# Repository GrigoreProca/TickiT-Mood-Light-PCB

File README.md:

# TickiT Mood Light PCB
DIY TickiT PCB with WS2812B LEDs

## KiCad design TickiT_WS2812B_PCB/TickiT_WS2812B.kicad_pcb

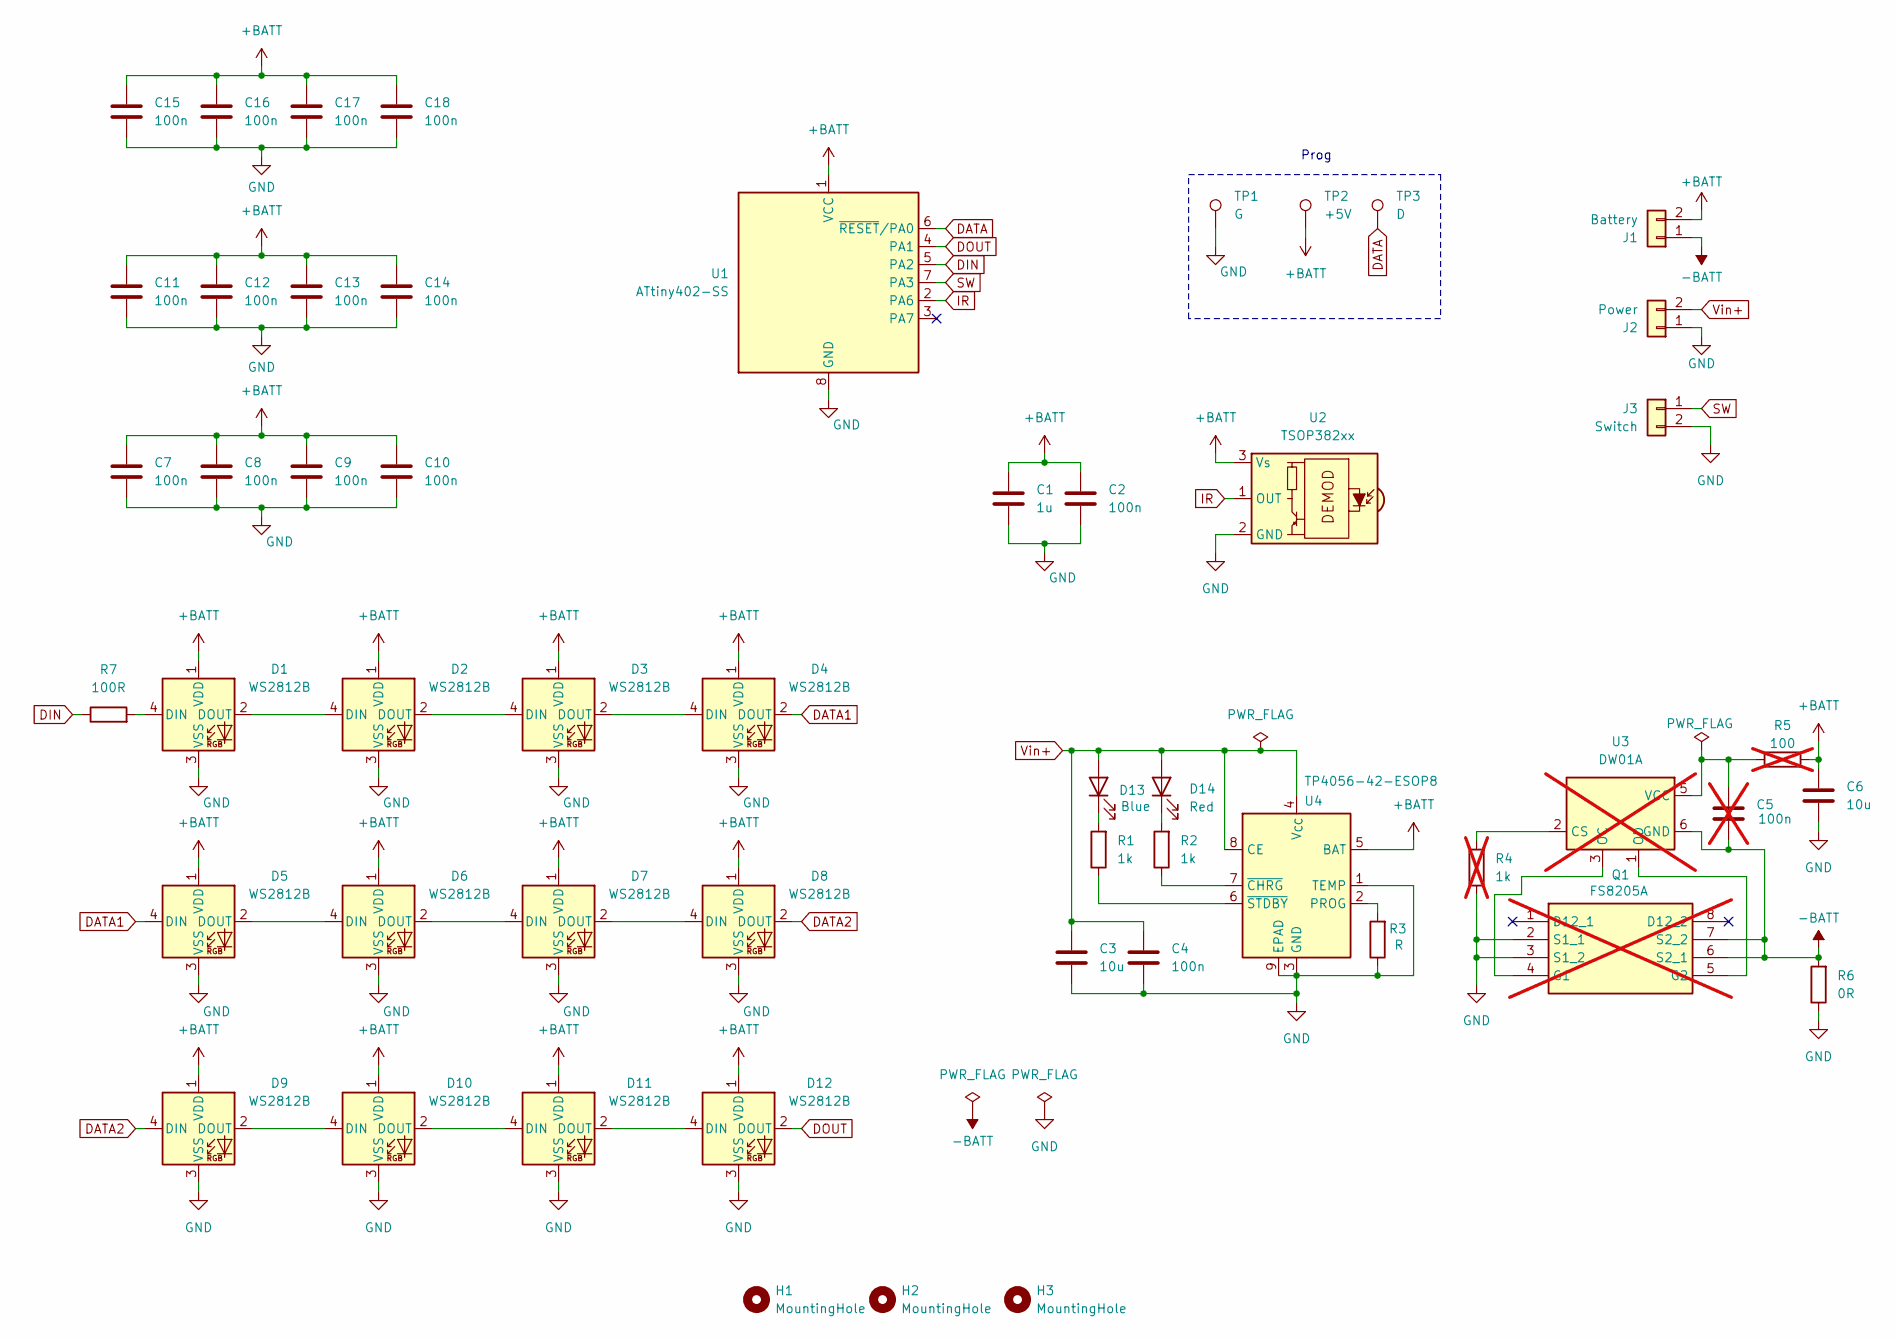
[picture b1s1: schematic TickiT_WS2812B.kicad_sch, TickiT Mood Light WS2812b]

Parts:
C1: 1u; C_0603_1608Metric_Pad1.08x0.95mm_HandSolder
C2, C4, C7, C8, C9, C10, C11, C12, C13, C14, C15, C16, C17, C18: 100n; C_0603_1608Metric_Pad1.08x0.95mm_HandSolder
C3, C6: 10u; C_0603_1608Metric_Pad1.08x0.95mm_HandSolder
C5: 100n; C_0603_1608Metric_Pad1.08x0.95mm_HandSolder; not fitted
D1, D2, D3, D4, D5, D6, D7, D8, D9, D10, D11, D12: WS2812B; LED_WS2812B_PLCC4_5.0x5.0mm_P3.2mm
D13: Blue; LED_0603_1608Metric_Pad1.05x0.95mm_HandSolder
D14: Red; LED_0603_1608Metric_Pad1.05x0.95mm_HandSolder
H1, H2, H3: MountingHole; MountingHole_3mm
J1: Battery; S2BPHSM4TBLFSN
J2: Power; S2BPHSM4TBLFSN
J3: Switch; S2BPHSM4TBLFSN
Q1: FS8205A; SOP65P640X120-8N; Manufacturer_Part_Number FS8205A; not fitted
R1, R2: 1k; R_0603_1608Metric_Pad0.98x0.95mm_HandSolder
R3: R; R_0603_1608Metric_Pad0.98x0.95mm_HandSolder
R4: 1k; R_0603_1608Metric_Pad0.98x0.95mm_HandSolder; not fitted
R5: 100; R_0603_1608Metric_Pad0.98x0.95mm_HandSolder; not fitted
R6: 0R; R_0603_1608Metric_Pad0.98x0.95mm_HandSolder
R7: 100R; R_0603_1608Metric_Pad0.98x0.95mm_HandSolder
TP1: G; TestPoint_Pad_D1.0mm
TP2: +5V; TestPoint_Pad_D1.0mm
TP3: D; TestPoint_Pad_D1.0mm
U1: ATtiny402-SS; SOIC-8_3.9x4.9mm_P1.27mm
U2: TSOP382xx; Vishay_MINICAST-3Pin
U3: DW01A; SOT-23-6; not fitted
U4: TP4056-42-ESOP8; SOIC-8-1EP_3.9x4.9mm_P1.27mm_EP2.41x3.3mm_ThermalVias

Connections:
+BATT: C1.1, C2.1, C6.1, C7.1, C8.1, C9.1, C10.1, C11.1, C12.1, C13.1, C14.1, C15.1, C16.1, C17.1, C18.1, D1.1 (VDD), D2.1 (VDD), D3.1 (VDD), D4.1 (VDD), D5.1 (VDD), D6.1 (VDD), D7.1 (VDD), D8.1 (VDD), D9.1 (VDD), D10.1 (VDD), D11.1 (VDD), D12.1 (VDD), J1.2, R5.2, TP2.1, U1.1 (VCC), U2.3 (Vs), U4.5 (BAT)
-BATT: C5.2, J1.1, Q1.6 (S2_1), Q1.7 (S2_2), R6.2, U3.6 (GND)
DATA: TP3.1, U1.6 (~RESET/PA0)
DATA1: D4.2 (DOUT), D5.4 (DIN)
DATA2: D8.2 (DOUT), D9.4 (DIN)
DIN: R7.1, U1.5 (PA2)
DOUT: D12.2 (DOUT), U1.4 (PA1)
GND: C1.2, C2.2, C3.2, C4.2, C6.2, C7.2, C8.2, C9.2, C10.2, C11.2, C12.2, C13.2, C14.2, C15.2, C16.2, C17.2, C18.2, D1.3 (VSS), D2.3 (VSS), D3.3 (VSS), D4.3 (VSS), D5.3 (VSS), D6.3 (VSS), D7.3 (VSS), D8.3 (VSS), D9.3 (VSS), D10.3 (VSS), D11.3 (VSS), D12.3 (VSS), J2.1, J3.2, Q1.2 (S1_1), Q1.3 (S1_2), R3.1, R4.1, R6.1, TP1.1, U1.8 (GND), U2.2 (GND), U4.1 (TEMP), U4.3 (GND), U4.9 (EPAD)
IR: U1.2 (PA6), U2.1 (OUT)
unnamed: D1.4 (DIN), R7.2
unnamed: D1.2 (DOUT), D2.4 (DIN)
unnamed: D2.2 (DOUT), D3.4 (DIN)
unnamed: D3.2 (DOUT), D4.4 (DIN)
unnamed: D5.2 (DOUT), D6.4 (DIN)
unnamed: D6.2 (DOUT), D7.4 (DIN)
unnamed: D7.2 (DOUT), D8.4 (DIN)
unnamed: D9.2 (DOUT), D10.4 (DIN)
unnamed: D10.2 (DOUT), D11.4 (DIN)
unnamed: D11.2 (DOUT), D12.4 (DIN)
unnamed: D13.1 (K), R1.2
unnamed: D14.1 (K), R2.2
unnamed: Q1.4 (G1), U3.3 (OC)
unnamed: Q1.5 (G2), U3.1 (OD)
unnamed: R4.2, U3.2 (CS)
unnamed: C5.1, R5.1, U3.5 (VCC)
unnamed: R3.2, U4.2 (PROG)
unnamed: R2.1, U4.7 (~CHRG)
unnamed: R1.1, U4.6 (~STDBY)
SW: J3.1, U1.7 (PA3)
Vin+: C3.1, C4.1, D13.2 (A), D14.2 (A), J2.2, U4.4 (V_{CC}), U4.8 (CE)

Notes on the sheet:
Prog

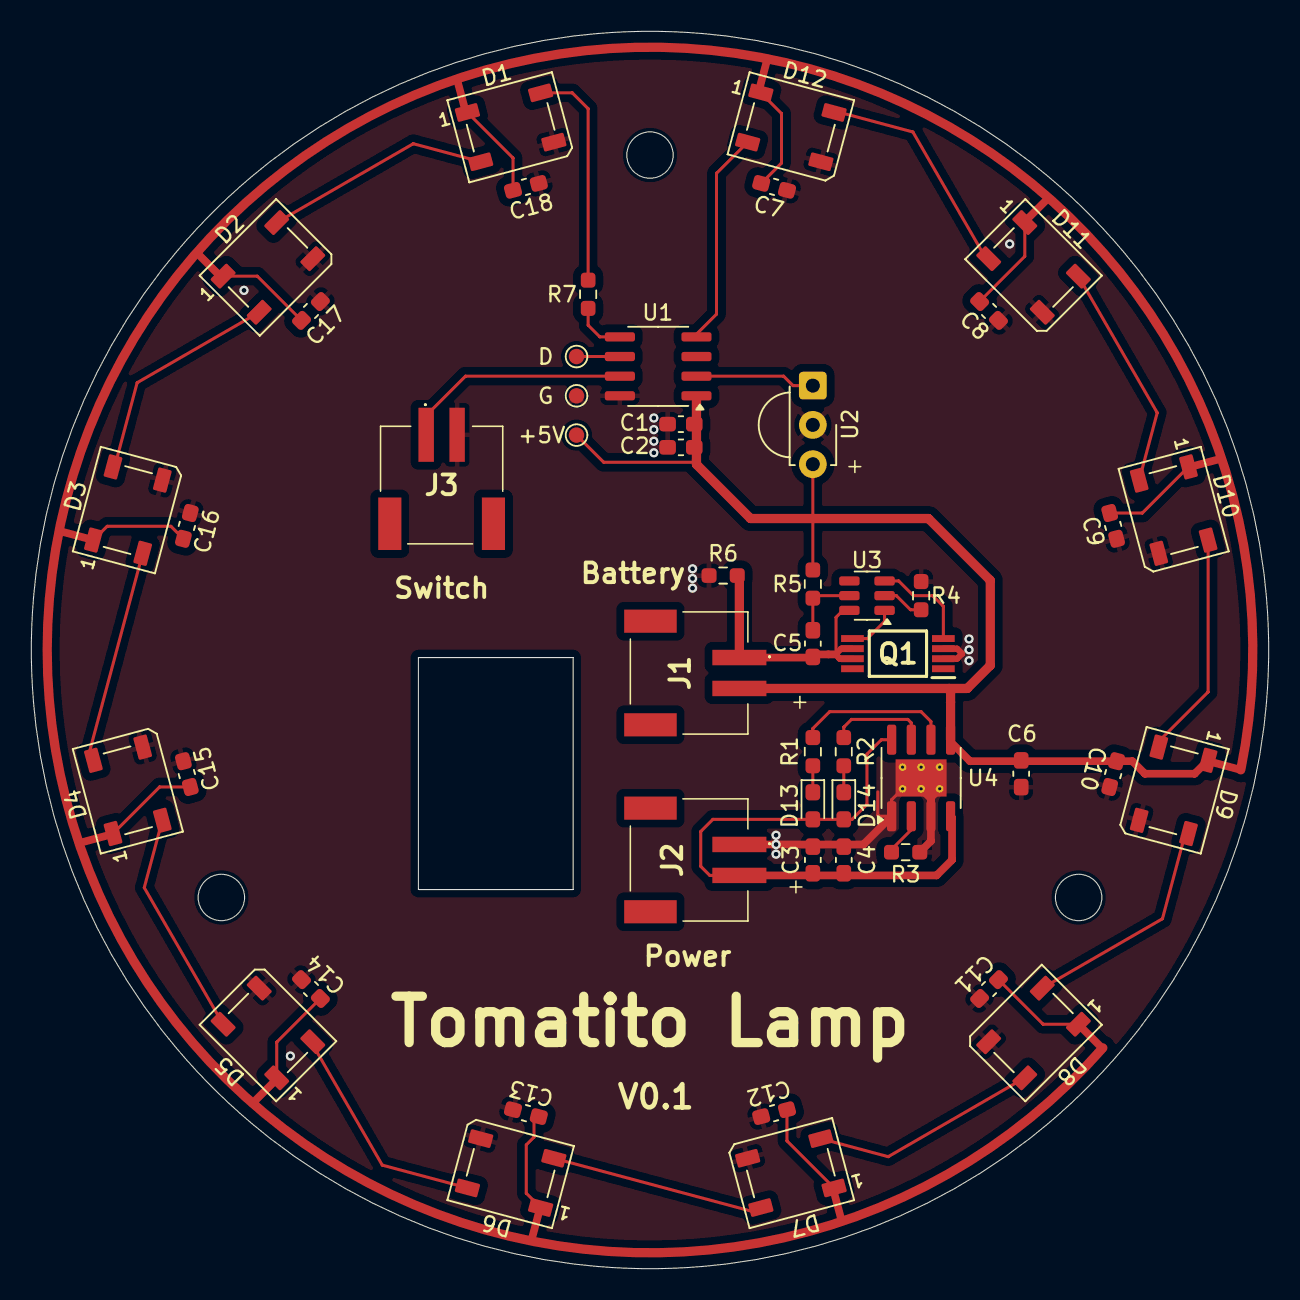
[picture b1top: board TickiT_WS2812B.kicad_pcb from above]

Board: 2 copper layers, 80.0 x 80.0 mm, 53 parts (0 on the bottom side), 30 nets.

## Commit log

2025-07-27 Add Firmware project
2025-07-27 change directory name
2025-07-27 add Docs folder
2025-07-27 add TickiT Instruction
2025-07-27 PCB routing
2025-09-03 PCB V0.1
